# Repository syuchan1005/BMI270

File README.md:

# BMI270 breakout board

|Front|Back|
|:-:|:-:|
|||

> !NOTE: All parts have LCS code and can be ordered PCBA at JLCPCB

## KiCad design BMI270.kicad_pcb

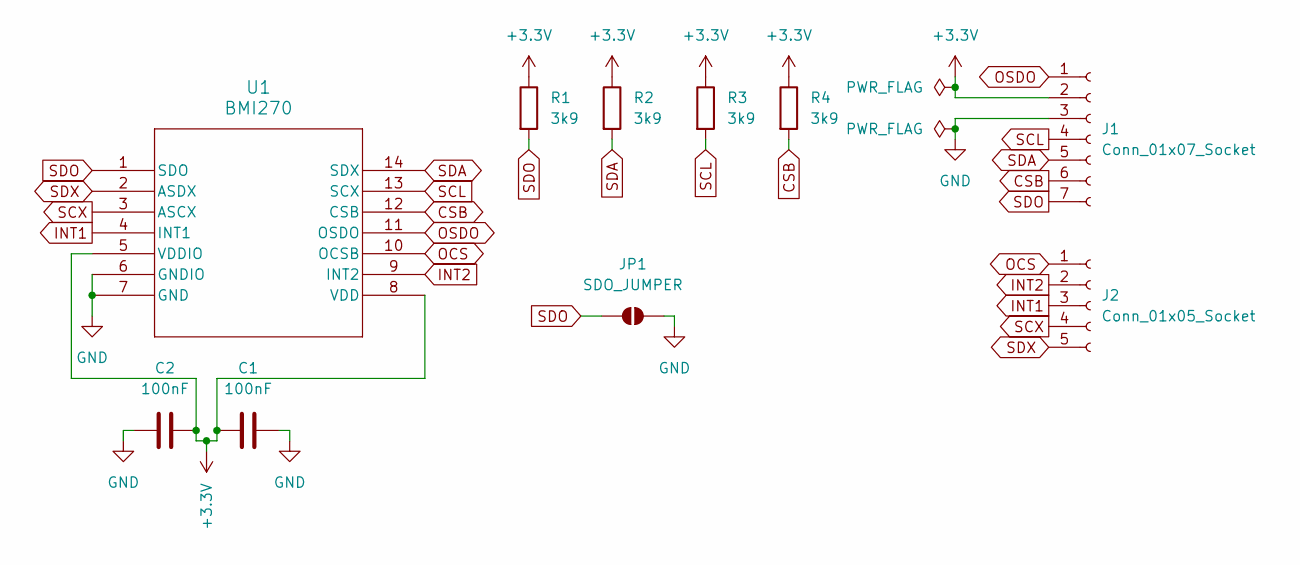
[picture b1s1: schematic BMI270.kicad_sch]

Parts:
C1, C2: 100nF; C_0603_1608Metric
J1: Conn_01x07_Socket; PinHeader_Castellated_1x07_P2.54mm_Vertical_142
J2: Conn_01x05_Socket; PinHeader_Castellated_1x05_P2.54mm_Vertical_142
JP1: SDO_JUMPER; SolderJumper-2_P1.3mm_Open_TrianglePad1.0x1.5mm
R1, R2, R3, R4: 3k9; R_0603_1608Metric
U1: BMI270; BMI270_BOS

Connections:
+3.3V: C1.1, C2.2, J1.2, R1.1, R2.1, R3.1, R4.1, U1.5 (VDDIO), U1.8 (VDD)
CSB: J1.6, R4.2, U1.12 (CSB)
GND: C1.2, C2.1, J1.3, JP1.2 (B), U1.6 (GNDIO), U1.7 (GND); also elsewhere on the board
INT1: J2.3, U1.4 (INT1)
INT2: J2.2, U1.9 (INT2)
OCS: J2.1, U1.10 (OCSB)
OSDO: J1.1, U1.11 (OSDO)
SCL: J1.4, R3.2, U1.13 (SCX)
SCX: J2.4, U1.3 (ASCX)
SDA: J1.5, R2.2, U1.14 (SDX)
SDO: J1.7, JP1.1 (A), R1.2, U1.1 (SDO); also elsewhere on the board
SDX: J2.5, U1.2 (ASDX)

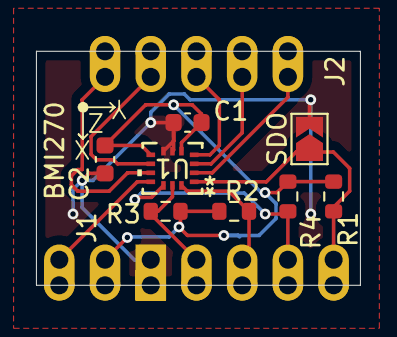
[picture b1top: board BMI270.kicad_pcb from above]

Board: 2 copper layers, 18.0 x 13.0 mm, 10 parts (1 on the bottom side), 12 nets.

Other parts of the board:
SDO: SDO_JUMPER; SolderJumper-2_P1.3mm_Open_TrianglePad1.0x1.5mm

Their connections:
GND: SDO.2 (B); also elsewhere on the board
SDO: SDO.1 (A); also elsewhere on the board

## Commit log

2024-11-05 init
2024-11-05 Fix labels
